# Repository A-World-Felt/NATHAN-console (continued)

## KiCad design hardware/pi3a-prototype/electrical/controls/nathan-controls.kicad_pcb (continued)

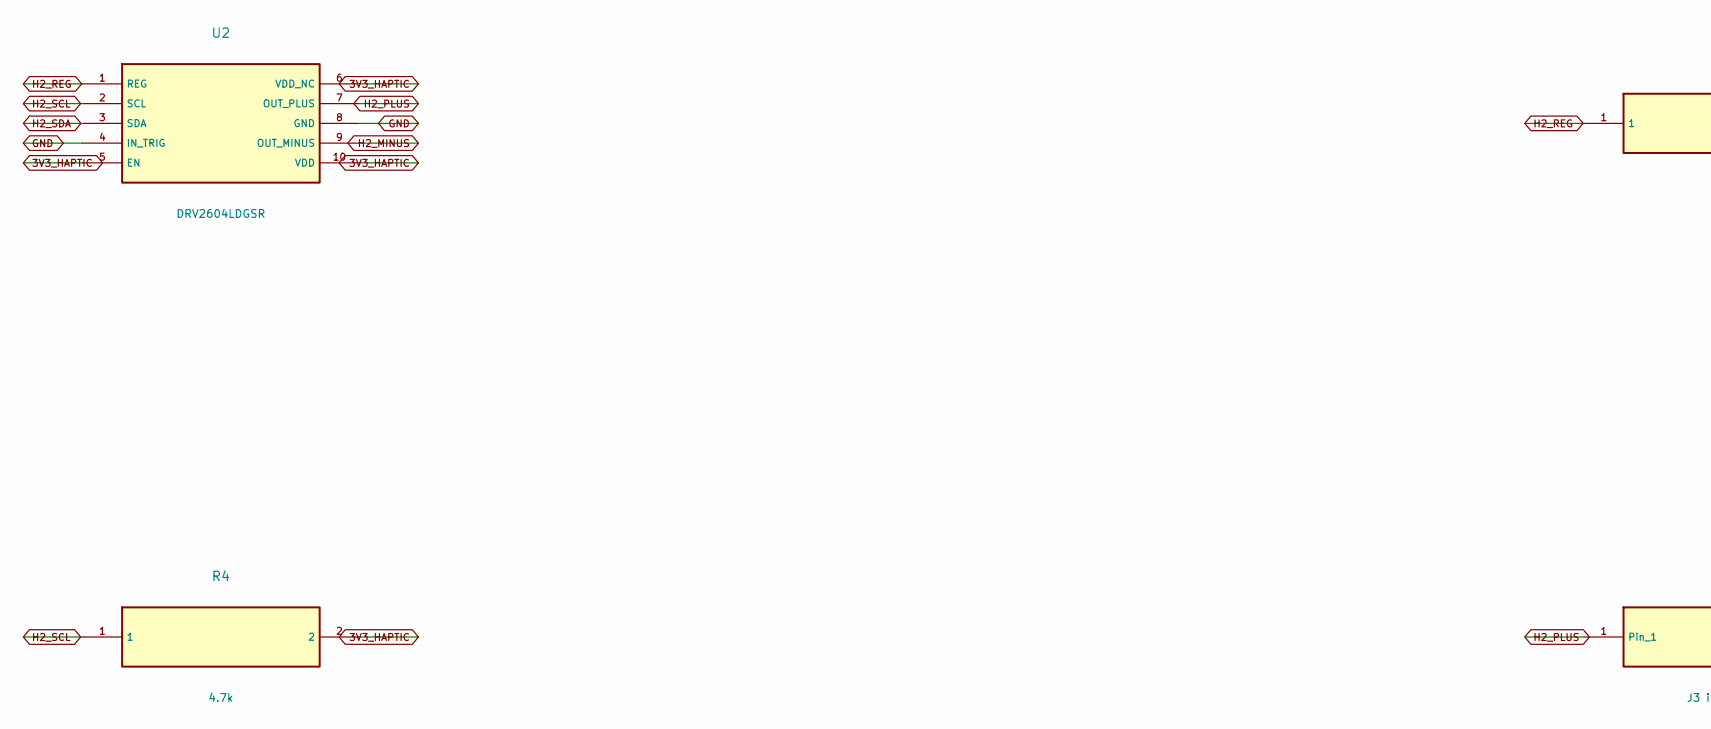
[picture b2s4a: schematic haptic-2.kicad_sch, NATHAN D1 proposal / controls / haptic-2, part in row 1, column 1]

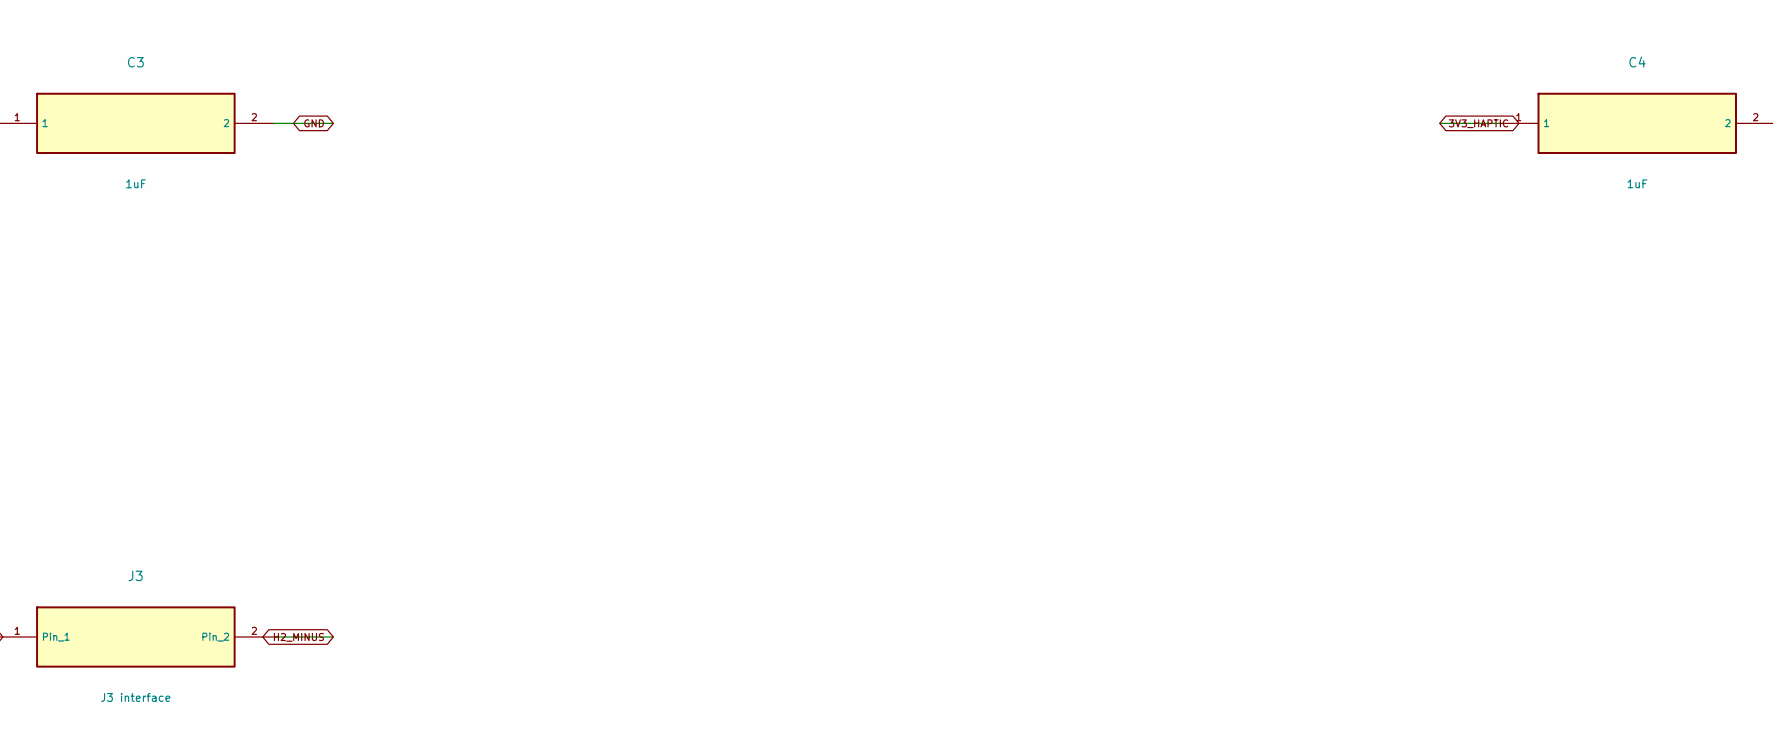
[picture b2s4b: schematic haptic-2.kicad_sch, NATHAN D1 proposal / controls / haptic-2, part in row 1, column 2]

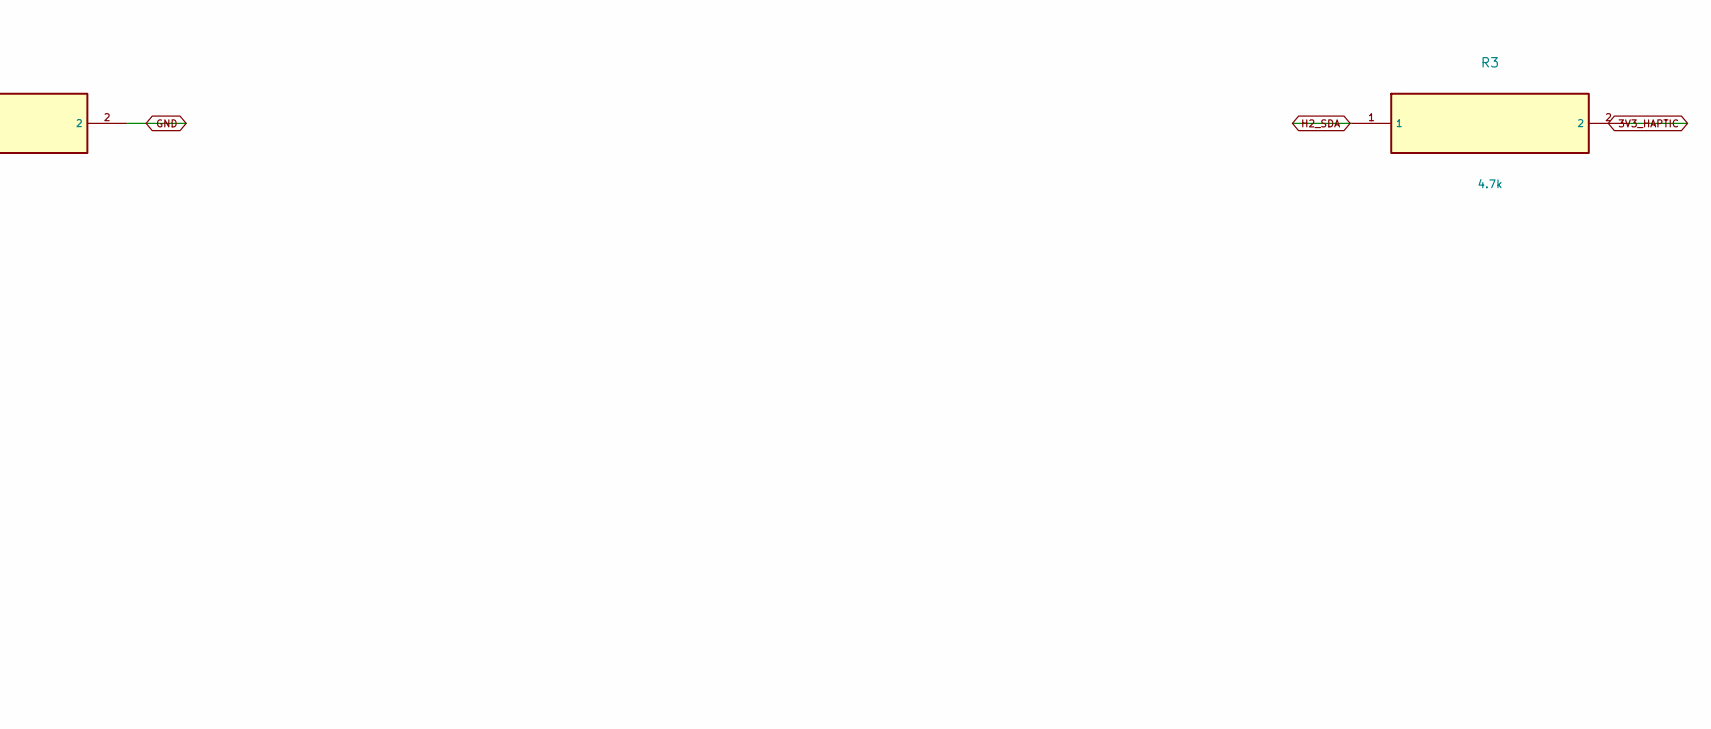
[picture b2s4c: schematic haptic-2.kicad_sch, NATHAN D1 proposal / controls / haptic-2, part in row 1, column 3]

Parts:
C3, C4: 1uF; C_0603_1608Metric
J3: J3 interface; JST_PH_B2B-PH-K_1x02_P2.00mm_Vertical
R3, R4: 4.7k; R_0603_1608Metric
U2: DRV2604LDGSR; VSSOP-10_3x3mm_P0.5mm

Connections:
3V3_HAPTIC: C4.1, R3.2, R4.2, U2.5 (EN), U2.6 (VDD_NC), U2.10 (VDD); also elsewhere on the board
GND: C3.2, C4.2, U2.4 (IN_TRIG), U2.8 (GND); also elsewhere on the board
H2_MINUS: J3.2, U2.9 (OUT_MINUS)
H2_PLUS: J3.1, U2.7 (OUT_PLUS)
H2_REG: C3.1, U2.1 (REG)
H2_SCL: R4.1, U2.2 (SCL); also elsewhere on the board
H2_SDA: R3.1, U2.3 (SDA); also elsewhere on the board

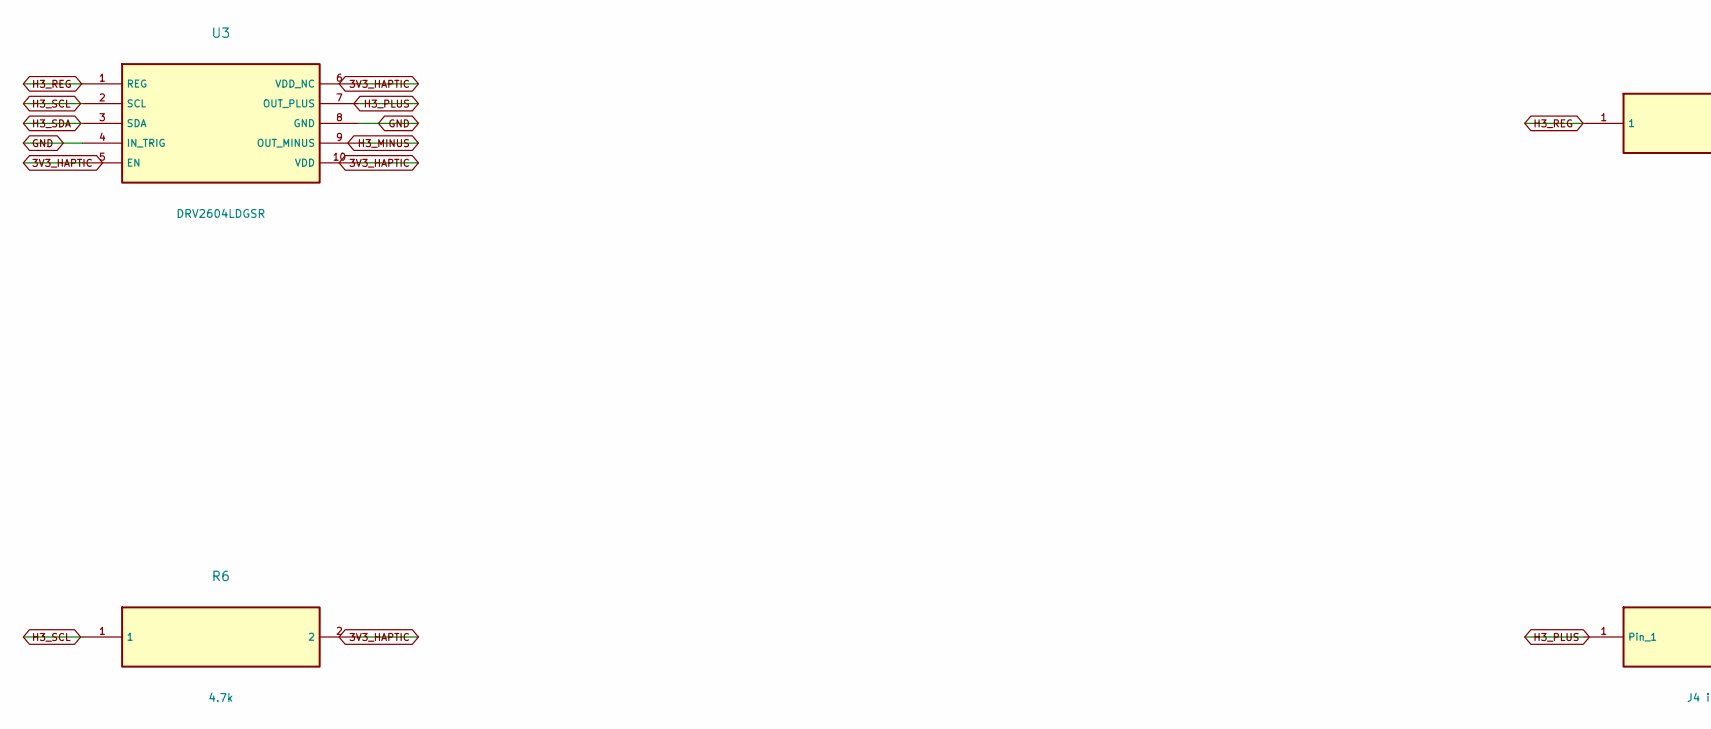
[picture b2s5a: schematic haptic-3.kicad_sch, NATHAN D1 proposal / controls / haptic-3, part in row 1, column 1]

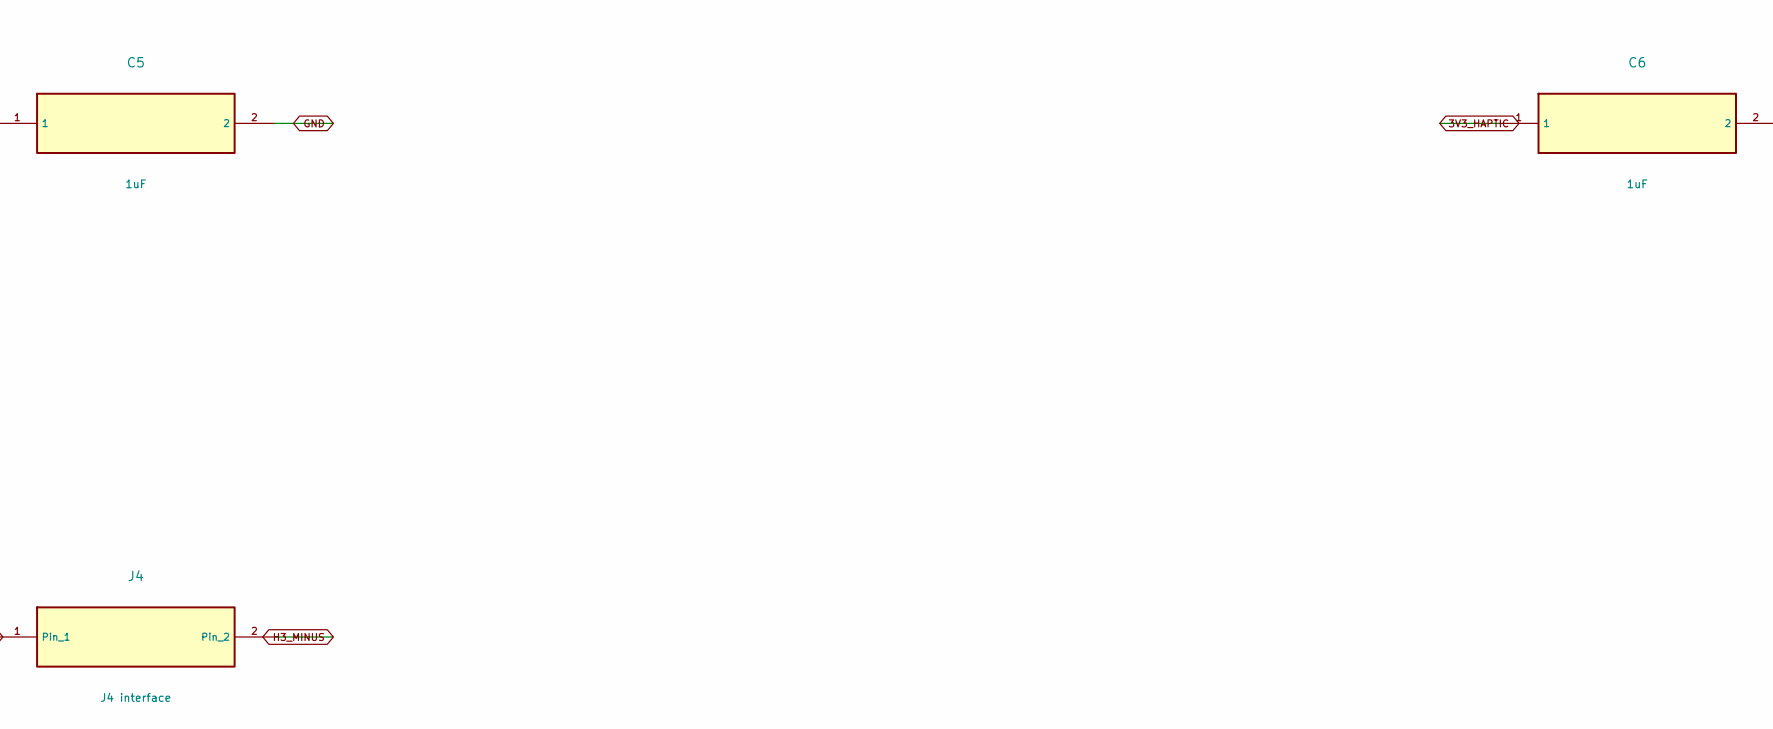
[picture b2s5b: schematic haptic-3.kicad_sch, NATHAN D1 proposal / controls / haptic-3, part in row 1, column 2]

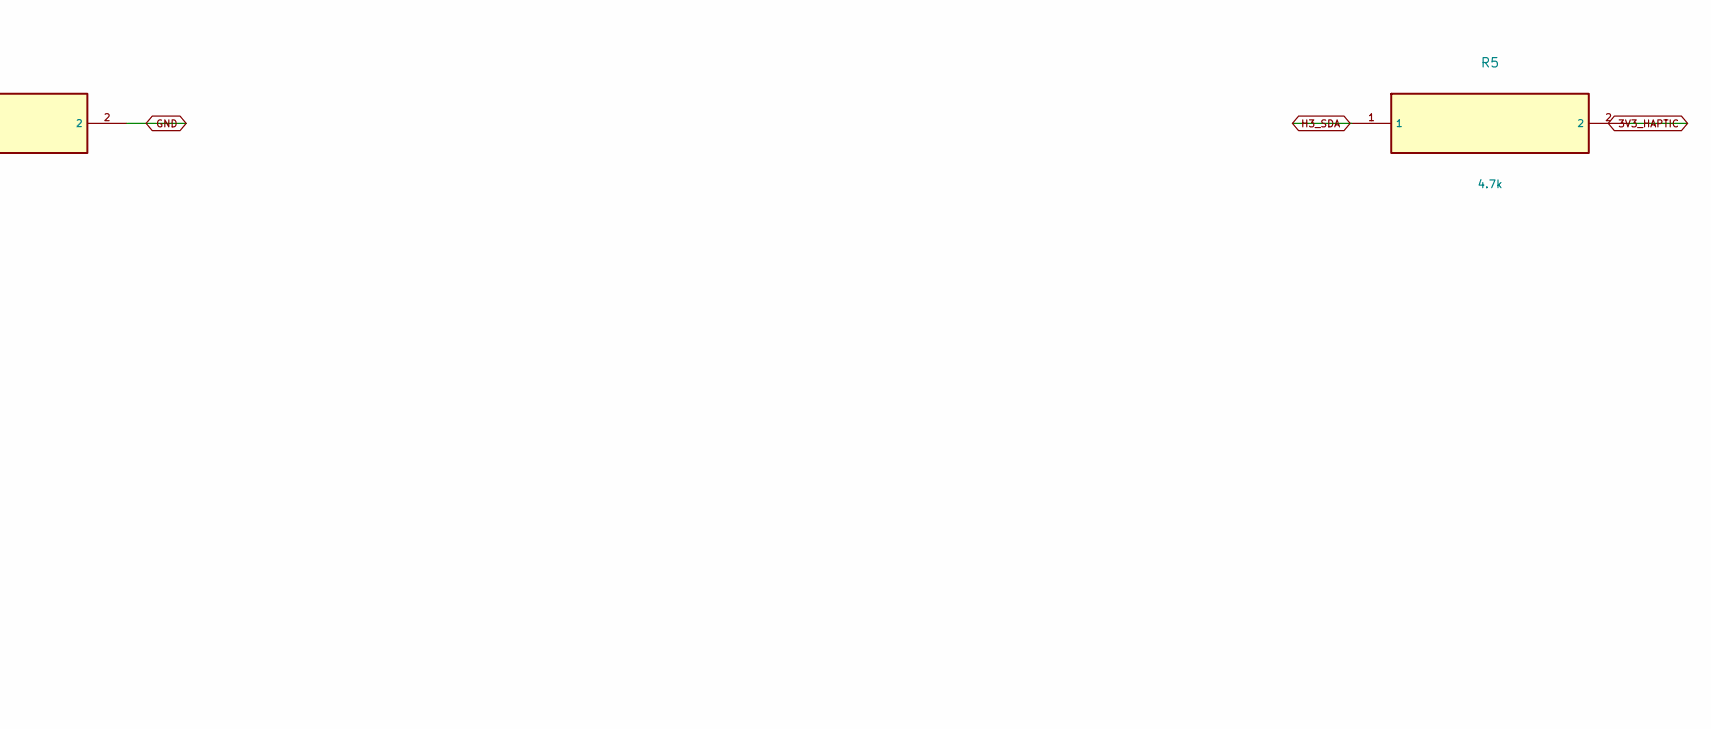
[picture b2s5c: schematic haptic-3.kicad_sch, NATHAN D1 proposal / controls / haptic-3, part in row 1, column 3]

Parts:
C5, C6: 1uF; C_0603_1608Metric
J4: J4 interface; JST_PH_B2B-PH-K_1x02_P2.00mm_Vertical
R5, R6: 4.7k; R_0603_1608Metric
U3: DRV2604LDGSR; VSSOP-10_3x3mm_P0.5mm

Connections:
3V3_HAPTIC: C6.1, R5.2, R6.2, U3.5 (EN), U3.6 (VDD_NC), U3.10 (VDD); also elsewhere on the board
GND: C5.2, C6.2, U3.4 (IN_TRIG), U3.8 (GND); also elsewhere on the board
H3_MINUS: J4.2, U3.9 (OUT_MINUS)
H3_PLUS: J4.1, U3.7 (OUT_PLUS)
H3_REG: C5.1, U3.1 (REG)
H3_SCL: R6.1, U3.2 (SCL); also elsewhere on the board
H3_SDA: R5.1, U3.3 (SDA); also elsewhere on the board

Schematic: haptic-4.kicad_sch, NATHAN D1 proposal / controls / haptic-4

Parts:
C7, C8: 1uF; C_0603_1608Metric
J5: J5 interface
R7, R8: 4.7k; R_0603_1608Metric
U4: DRV2604LDGSR; VSSOP-10_3x3mm_P0.5mm

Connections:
3V3_HAPTIC: C8.1, R7.2, R8.2, U4.5 (EN), U4.6 (VDD_NC), U4.10 (VDD); also elsewhere on the board
GND: C7.2, C8.2, U4.4 (IN_TRIG), U4.8 (GND); also elsewhere on the board
H4_MINUS: J5.2, U4.9 (OUT_MINUS)
H4_PLUS: J5.1, U4.7 (OUT_PLUS)
H4_REG: C7.1, U4.1 (REG)
H4_SCL: R8.1, U4.2 (SCL); also elsewhere on the board
H4_SDA: R7.1, U4.3 (SDA); also elsewhere on the board

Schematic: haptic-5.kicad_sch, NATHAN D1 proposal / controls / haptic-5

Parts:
C9, C10: 1uF; C_0603_1608Metric
J6: J6 interface; JST_PH_B2B-PH-K_1x02_P2.00mm_Vertical
R9, R10: 4.7k; R_0603_1608Metric
U5: DRV2604LDGSR; VSSOP-10_3x3mm_P0.5mm

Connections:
3V3_HAPTIC: C10.1, R9.2, R10.2, U5.5 (EN), U5.6 (VDD_NC), U5.10 (VDD); also elsewhere on the board
GND: C9.2, C10.2, U5.4 (IN_TRIG), U5.8 (GND); also elsewhere on the board
H5_MINUS: J6.2, U5.9 (OUT_MINUS)
H5_PLUS: J6.1, U5.7 (OUT_PLUS)
H5_REG: C9.1, U5.1 (REG)
H5_SCL: R10.1, U5.2 (SCL); also elsewhere on the board
H5_SDA: R9.1, U5.3 (SDA); also elsewhere on the board

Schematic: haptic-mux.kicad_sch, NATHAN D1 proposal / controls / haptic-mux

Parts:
C18: 100nF; C_0603_1608Metric
U8: TCA9548APWR; TSSOP-24_4.4x7.8mm_P0.65mm

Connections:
3V3_PI: C18.1, U8.24 (VCC); also elsewhere on the board
CTRL_RESET_N: U8.3 (RESET_N); also elsewhere on the board
GND: C18.2, U8.1 (A0), U8.2 (A1), U8.12 (GND), U8.21 (A2); also elsewhere on the board
H1_SCL: U8.5 (SC0); also elsewhere on the board
H1_SDA: U8.4 (SD0); also elsewhere on the board
H2_SCL: U8.7 (SC1); also elsewhere on the board
H2_SDA: U8.6 (SD1); also elsewhere on the board
H3_SCL: U8.9 (SC2); also elsewhere on the board
H3_SDA: U8.8 (SD2); also elsewhere on the board
H4_SCL: U8.11 (SC3); also elsewhere on the board
H4_SDA: U8.10 (SD3); also elsewhere on the board
H5_SCL: U8.14 (SC4); also elsewhere on the board
H5_SDA: U8.13 (SD4); also elsewhere on the board
I2C_SCL: U8.22 (SCL); also elsewhere on the board
I2C_SDA: U8.23 (SDA); also elsewhere on the board

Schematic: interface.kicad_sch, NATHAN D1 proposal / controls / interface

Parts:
C13: 100nF; C_0603_1608Metric
C14: 1uF; C_0603_1608Metric
J100: J100 interface; IDC-Header_2x08_P2.54mm_Vertical
R11, R12: 4.7k DNP; R_0603_1608Metric; not fitted
R13, R14, R15: 10k; R_0603_1608Metric

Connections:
3V3_PI: C14.1, J100.15, R11.2, R12.2, R13.2, R14.2, R15.2; also elsewhere on the board
5V_SYS: J100.1, J100.2; also elsewhere on the board
ADC_CS_N: J100.13, R15.1; also elsewhere on the board
CTRL_RESET_N: C13.1, J100.16, R13.1; also elsewhere on the board
GND: C13.2, C14.2, J100.3, J100.4, J100.7, J100.10, J100.14; also elsewhere on the board
I2C_SCL: J100.6, R12.1; also elsewhere on the board
I2C_SDA: J100.5, R11.1; also elsewhere on the board
INPUT_IRQ_N: J100.8, R14.1; also elsewhere on the board
SPI_MISO: J100.12; also elsewhere on the board
SPI_MOSI: J100.11; also elsewhere on the board
SPI_SCLK: J100.9; also elsewhere on the board

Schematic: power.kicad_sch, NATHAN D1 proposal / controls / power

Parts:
C30: 10uF 10V X5R; C_0805_2012Metric
C31: 22uF 6.3V X5R; C_0805_2012Metric
L1: 1uH XAL4020-102MEC candidate; L_Coilcraft_XAL4020-XXX
PS2: TPS62080DSGR; WSON-8-1EP_2x2mm_P0.5mm_EP0.9x1.6mm
R60: 249k 1%; R_0603_1608Metric
R61: 39.2k 1%; R_0603_1608Metric

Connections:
3V3_HAPTIC: C31.1, L1.2, PS2.5 (VOS), R60.1; also elsewhere on the board
5V_SYS: C30.1, PS2.1 (EN), PS2.8 (VIN); also elsewhere on the board
GND: C30.2, C31.2, PS2.2 (GND), PS2.3 (MODE), PS2.9 (EP), R61.2; also elsewhere on the board
HAPTIC_FB: PS2.4 (FB), R60.2, R61.1
HAPTIC_SW: L1.1, PS2.7 (SW)

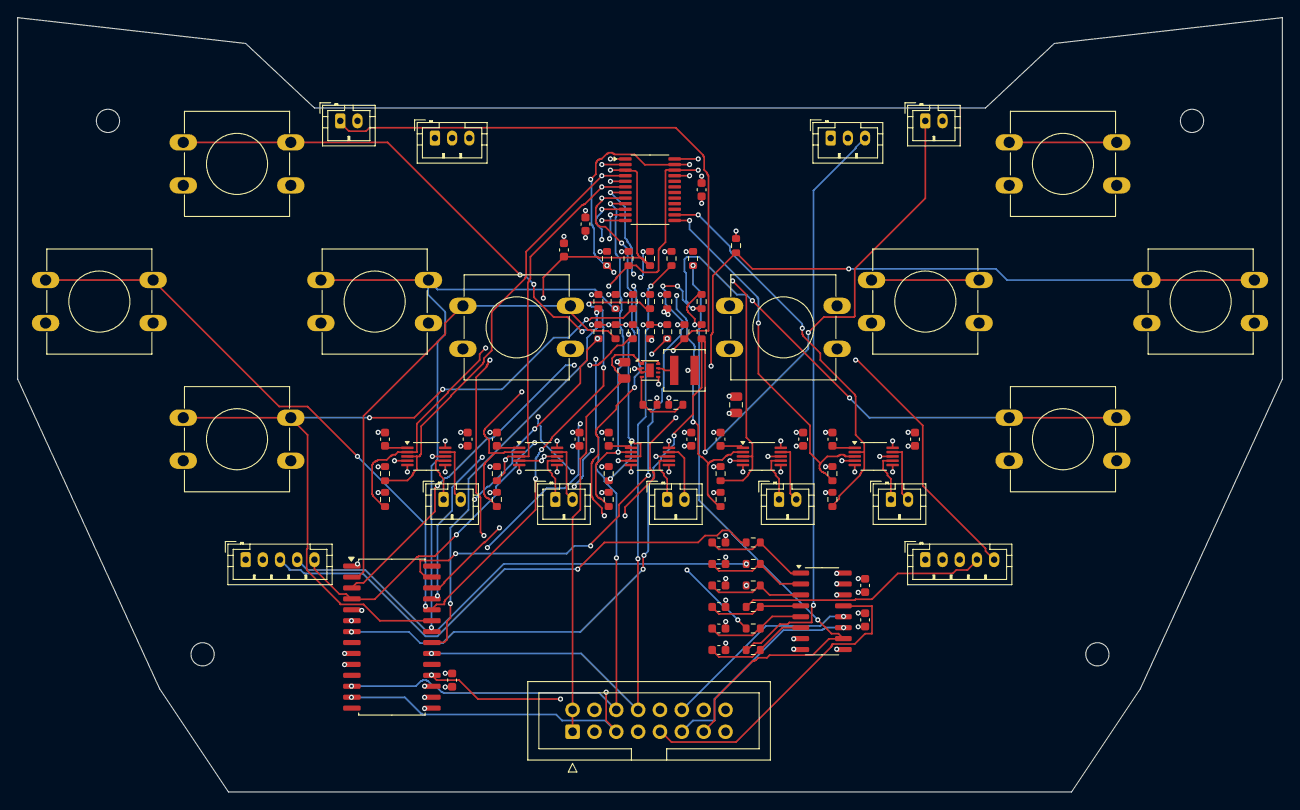
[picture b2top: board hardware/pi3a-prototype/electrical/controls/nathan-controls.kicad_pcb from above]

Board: 4 copper layers, 147.0 x 90.0 mm, 97 parts (0 on the bottom side), 65 nets.

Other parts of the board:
H1, H2, H3, H4: MountingHole_2.7mm_M2.5

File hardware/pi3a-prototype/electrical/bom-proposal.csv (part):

board,reference,value,footprint,dnp,source,qualification_note
controls,J100,J100 interface,Connector_IDC:IDC-Header_2x08_P2.54mm_Vertical,False,design proposal,Proposed keyed 16-way signal cable; 5 V supply contact/current and cable assembly qualification pending. Pins 15/16 change D0 reserved assignments.
controls,R11,4.7k DNP,Resistor_SMD:R_0603_1608Metric,True,design proposal,DNP until total Pi/PiSugar pullup network is measured
controls,R12,4.7k DNP,Resistor_SMD:R_0603_1608Metric,True,design proposal,DNP until total Pi/PiSugar pullup network is measured
controls,R13,10k,Resistor_SMD:R_0603_1608Metric,False,design proposal,
controls,R14,10k,Resistor_SMD:R_0603_1608Metric,False,design proposal,
controls,R15,10k,Resistor_SMD:R_0603_1608Metric,False,design proposal,
controls,C13,100nF,Capacitor_SMD:C_0603_1608Metric,False,design proposal,
controls,C14,1uF,Capacitor_SMD:C_0603_1608Metric,False,design proposal,
controls,U7,MCP23017-E/SO,Package_SO:SOIC-28W_7.5x17.9mm_P1.27mm,False,MCP23017,0x20. Configure GPA7/GPB7 outputs low; mirror both interrupt banks into INTA; INTB left open. Verify manufacturer land pattern before routing.
controls,C15,100nF,Capacitor_SMD:C_0603_1608Metric,False,design proposal,
controls,R30,10k,Resistor_SMD:R_0603_1608Metric,False,design proposal,
controls,SW2,B3F-4055 candidate,Button_Switch_THT:SW_PUSH-12mm,False,design proposal,Ten existing BOM buttons: 8 face + 2 central. Candidate footprint still to qualify.
controls,R31,10k,Resistor_SMD:R_0603_1608Metric,False,design proposal,
controls,SW3,B3F-4055 candidate,Button_Switch_THT:SW_PUSH-12mm,False,design proposal,Ten existing BOM buttons: 8 face + 2 central. Candidate footprint still to qualify.
controls,R32,10k,Resistor_SMD:R_0603_1608Metric,False,design proposal,
controls,SW4,B3F-4055 candidate,Button_Switch_THT:SW_PUSH-12mm,False,design proposal,Ten existing BOM buttons: 8 face + 2 central. Candidate footprint still to qualify.
controls,R33,10k,Resistor_SMD:R_0603_1608Metric,False,design proposal,
controls,SW5,B3F-4055 candidate,Button_Switch_THT:SW_PUSH-12mm,False,design proposal,Ten existing BOM buttons: 8 face + 2 central. Candidate footprint still to qualify.
controls,R34,10k,Resistor_SMD:R_0603_1608Metric,False,design proposal,
controls,SW6,B3F-4055 candidate,Button_Switch_THT:SW_PUSH-12mm,False,design proposal,Ten existing BOM buttons: 8 face + 2 central. Candidate footprint still to qualify.
controls,R35,10k,Resistor_SMD:R_0603_1608Metric,False,design proposal,
controls,SW7,B3F-4055 candidate,Button_Switch_THT:SW_PUSH-12mm,False,design proposal,Ten existing BOM buttons: 8 face + 2 central. Candidate footprint still to qualify.
controls,R36,10k,Resistor_SMD:R_0603_1608Metric,False,design proposal,
controls,SW8,B3F-4055 candidate,Button_Switch_THT:SW_PUSH-12mm,False,design proposal,Ten existing BOM buttons: 8 face + 2 central. Candidate footprint still to qualify.
controls,R37,10k,Resistor_SMD:R_0603_1608Metric,False,design proposal,
controls,SW9,B3F-4055 candidate,Button_Switch_THT:SW_PUSH-12mm,False,design proposal,Ten existing BOM buttons: 8 face + 2 central. Candidate footprint still to qualify.
controls,R38,10k,Resistor_SMD:R_0603_1608Metric,False,design proposal,
controls,SW10,B3F-4055 candidate,Button_Switch_THT:SW_PUSH-12mm,False,design proposal,Ten existing BOM buttons: 8 face + 2 central. Candidate footprint still to qualify.
controls,R39,10k,Resistor_SMD:R_0603_1608Metric,False,design proposal,
controls,SW11,B3F-4055 candidate,Button_Switch_THT:SW_PUSH-12mm,False,design proposal,Ten existing BOM buttons: 8 face + 2 central. Candidate footprint still to qualify.
controls,R40,10k,Resistor_SMD:R_0603_1608Metric,False,design proposal,
controls,R41,10k,Resistor_SMD:R_0603_1608Metric,False,design proposal,
controls,R42,10k,Resistor_SMD:R_0603_1608Metric,False,design proposal,
controls,R43,10k,Resistor_SMD:R_0603_1608Metric,False,design proposal,
controls,U6,MCP3208-CI/SL,Package_SO:SOIC-16_3.9x9.9mm_P1.27mm,False,MCP3208,Proposed 12-bit replacement for MCP3008. SPI command framing changes; not software drop-in. Six ratiometric channels.
controls,C16,100nF,Capacitor_SMD:C_0603_1608Metric,False,design proposal,
controls,C17,1uF,Capacitor_SMD:C_0603_1608Metric,False,design proposal,
controls,R50,100R,Resistor_SMD:R_0603_1608Metric,False,design proposal,
controls,C20,1nF,Capacitor_SMD:C_0603_1608Metric,False,design proposal,"Initial filter candidate; settle/error must be measured with actual sensor. Start SPI at 100 kHz, dummy conversion after channel change."
controls,R51,100R,Resistor_SMD:R_0603_1608Metric,False,design proposal,
controls,C21,1nF,Capacitor_SMD:C_0603_1608Metric,False,design proposal,"Initial filter candidate; settle/error must be measured with actual sensor. Start SPI at 100 kHz, dummy conversion after channel change."
controls,R52,100R,Resistor_SMD:R_0603_1608Metric,False,design proposal,
controls,C22,1nF,Capacitor_SMD:C_0603_1608Metric,False,design proposal,"Initial filter candidate; settle/error must be measured with actual sensor. Start SPI at 100 kHz, dummy conversion after channel change."
controls,R53,100R,Resistor_SMD:R_0603_1608Metric,False,design proposal,
controls,C23,1nF,Capacitor_SMD:C_0603_1608Metric,False,design proposal,"Initial filter candidate; settle/error must be measured with actual sensor. Start SPI at 100 kHz, dummy conversion after channel change."
controls,R54,100R,Resistor_SMD:R_0603_1608Metric,False,design proposal,
controls,C24,1nF,Capacitor_SMD:C_0603_1608Metric,False,design proposal,"Initial filter candidate; settle/error must be measured with actual sensor. Start SPI at 100 kHz, dummy conversion after channel change."
controls,R55,100R,Resistor_SMD:R_0603_1608Metric,False,design proposal,
controls,C25,1nF,Capacitor_SMD:C_0603_1608Metric,False,design proposal,"Initial filter candidate; settle/error must be measured with actual sensor. Start SPI at 100 kHz, dummy conversion after channel change."
controls,J20,J20 interface,,False,design proposal,"Joystick left interface, not COM-09032 physical pin numbering"
controls,J21,J21 interface,,False,design proposal,"Joystick right interface, not COM-09032 physical pin numbering"
controls,J22,J22 interface,,False,design proposal,Analog trigger left; sensor and pivot not selected
controls,J23,J23 interface,,False,design proposal,Analog trigger right; sensor and pivot not selected
controls,J24,J24 interface,,False,design proposal,Additional left shoulder switch beyond workbook quantities
controls,J25,J25 interface,,False,design proposal,Additional right shoulder switch beyond workbook quantities
controls,U8,TCA9548APWR,Package_SO:TSSOP-24_4.4x7.8mm_P0.65mm,False,TCA9548A,"Address 0x70; channels 0-4 used, 5-7 unconnected. Select one channel for each transaction with 0x5A devices."
controls,C18,100nF,Capacitor_SMD:C_0603_1608Metric,False,design proposal,
controls,U1,DRV2604LDGSR,Package_SO:VSSOP-10_3x3mm_P0.5mm,False,DRV2604L,"EN follows motor rail; I2C runtime/standby control. OUT_MINUS is a differential output, never ground. LRA rated voltage must be configured separately."
controls,C1,1uF,Capacitor_SMD:C_0603_1608Metric,False,design proposal,
controls,C2,1uF,Capacitor_SMD:C_0603_1608Metric,False,design proposal,
controls,R1,4.7k,Resistor_SMD:R_0603_1608Metric,False,design proposal,
controls,R2,4.7k,Resistor_SMD:R_0603_1608Metric,False,design proposal,
controls,J2,J2 interface,,False,design proposal,VG0832013D cable interface; exact keyed connector/counterpart pending
controls,U2,DRV2604LDGSR,Package_SO:VSSOP-10_3x3mm_P0.5mm,False,DRV2604L,"EN follows motor rail; I2C runtime/standby control. OUT_MINUS is a differential output, never ground. LRA rated voltage must be configured separately."
controls,C3,1uF,Capacitor_SMD:C_0603_1608Metric,False,design proposal,
controls,C4,1uF,Capacitor_SMD:C_0603_1608Metric,False,design proposal,
controls,R3,4.7k,Resistor_SMD:R_0603_1608Metric,False,design proposal,
controls,R4,4.7k,Resistor_SMD:R_0603_1608Metric,False,design proposal,
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
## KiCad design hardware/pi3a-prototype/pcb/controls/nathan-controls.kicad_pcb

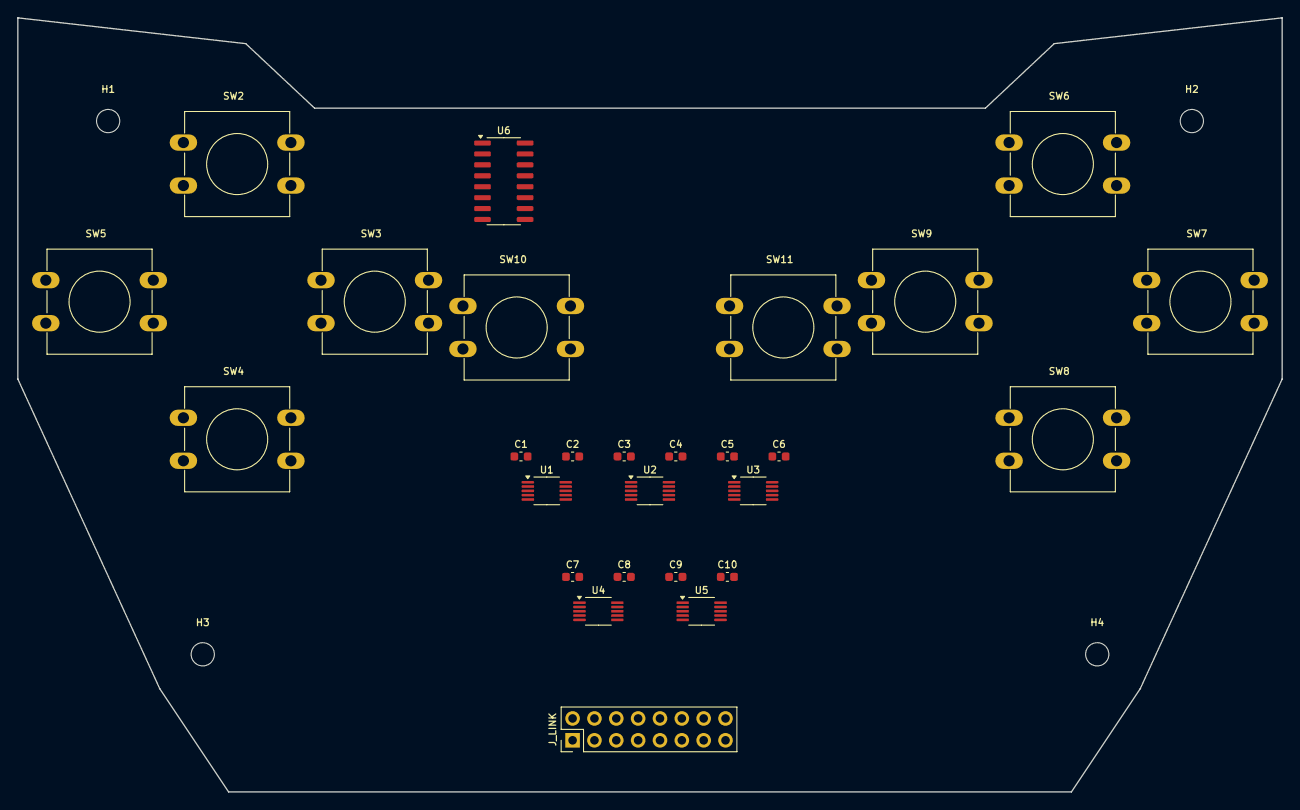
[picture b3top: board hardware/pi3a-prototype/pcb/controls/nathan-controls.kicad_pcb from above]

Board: 2 copper layers, 147.0 x 90.0 mm, 31 parts (0 on the bottom side), 2 nets, no tracks yet.

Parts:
C1, C2, C3, C4, C5, C6, C7, C8, C9, C10: 1uF - voltage/tolerance TBD; C_0603_1608Metric
H1, H2, H3, H4: PROPOSED M2.5; MountingHole_2.7mm_M2.5
J_LINK: PROPOSED 2x08 - MPN TBD; PinHeader_2x08_P2.54mm_Vertical
SW2, SW3, SW4, SW5, SW6, SW7, SW8, SW9, SW10, SW11: B3F-4055 candidate - VERIFY DRAWING; SW_PUSH-12mm
U1, U2, U3, U4, U5: DRV2604LDGSR; VSSOP-10_3x3mm_P0.5mm
U6: MCP3008-I/SL; SOIC-16_3.9x9.9mm_P1.27mm

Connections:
5V_SYS: J_LINK.1, J_LINK.2
GND: J_LINK.3, J_LINK.4, J_LINK.7, J_LINK.10, J_LINK.14

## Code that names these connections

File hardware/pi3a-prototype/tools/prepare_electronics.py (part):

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    for i,name in enumerate(adc):
        passive(b,'analog','R'+str(50+i),'100R','RAW_'+name,'ADC_'+name)
        passive(b,'analog','C'+str(20+i),'1nF','ADC_'+name,'GND',note='Initial filter candidate; settle/error must be measured with actual sensor. Start SPI at 100 kHz, dummy conversion after channel change.')
    conn(b,'analog','J20',['3V3_PI','GND','RAW_LX','RAW_LY','STICK_L_CLICK'],note='Joystick left interface, not COM-09032 physical pin numbering')
    conn(b,'analog','J21',['3V3_PI','GND','RAW_RX','RAW_RY','STICK_R_CLICK'],note='Joystick right interface, not COM-09032 physical pin numbering')
    conn(b,'analog','J22',['3V3_PI','GND','RAW_L2'],note='Analog trigger left; sensor and pivot not selected')
    conn(b,'analog','J23',['3V3_PI','GND','RAW_R2'],note='Analog trigger right; sensor and pivot not selected')
    conn(b,'digital','J24',['SHOULDER_L1','GND'],note='Additional left shoulder switch beyond workbook quantities')
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
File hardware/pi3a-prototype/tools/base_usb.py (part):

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        ('2N7002', 'https://assets.nexperia.com/documents/data-sheet/2N7002.pdf', 'Rev 7', '1'),
    ]
}
PI_PHYSICAL_PINS = {29: 'USB_CHARGE_RUN', 31: 'USB_CHARGE_CLOCK'}
LOCAL_LIBRARY = 'NATHAN_USB'


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        passive(b, sheet, ref, value, net, 'GND', footprint=footprint, note=note)

    # GCT footprint has overlapping same-net A/B power contacts and four S1 pads.
    mapping = {'A1': 'GND', 'A4': 'USB_PC_VBUS', 'A5': 'USB_CC1',
               'A6': 'USB_PC_DP', 'A7': 'USB_PC_DM', 'A8': None,
               'A9': 'USB_PC_VBUS', 'A12': 'GND', 'B1': 'GND',
               'B4': 'USB_PC_VBUS', 'B5': 'USB_CC2', 'B6': 'USB_PC_DP',
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
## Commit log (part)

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2025-06-21 squash
2025-06-22 CAD Files
2025-06-22 BOM update
2025-06-25 Add initial KiCAD project files for GlassBreaker PCB design
    - Created GlassBreaker_KiCAD.kicad_prl for project layer settings.
    - Added GlassBreaker_KiCAD.kicad_pro containing board design settings and rules.
    - Introduced fp-info-cache file for footprint information.
    - Generated lock file ~GlassBreaker_KiCAD.kicad_pcb.lck to manage project access.
2025-06-25 Add initial KiCad project files for NATHAN-pcb
    - Created NATHAN-pcb.kicad_prl with board settings and visibility options.
    - Added NATHAN-pcb.kicad_pro containing comprehensive design settings, net settings, and rules for PCB layout.
    - Introduced lock file ~NATHAN-pcb.kicad_pcb.lck to manage project access.
2025-06-25 Add footprint information for Reverb modules and create autosave lock file
    - Added fp-info-cache for two Reverb modules (BTDR-1H and BTDR-1V) with relevant details and links.
    - Created an autosave lock file for the KiCAD project to prevent concurrent edits.
2025-06-25 Remove GlassBreaker KiCAD project file
2025-08-28 docs: update ReadMe
2025-09-22 doc: fix readMe
2025-09-22 fix: pcb errors
2026-03-04 feat: add Cahier des charges
2026-03-05 feat: update CAHIER-DES-CHARGES
